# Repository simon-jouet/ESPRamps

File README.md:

# ESPRamps

ESP32 3d printer board for RAMPS

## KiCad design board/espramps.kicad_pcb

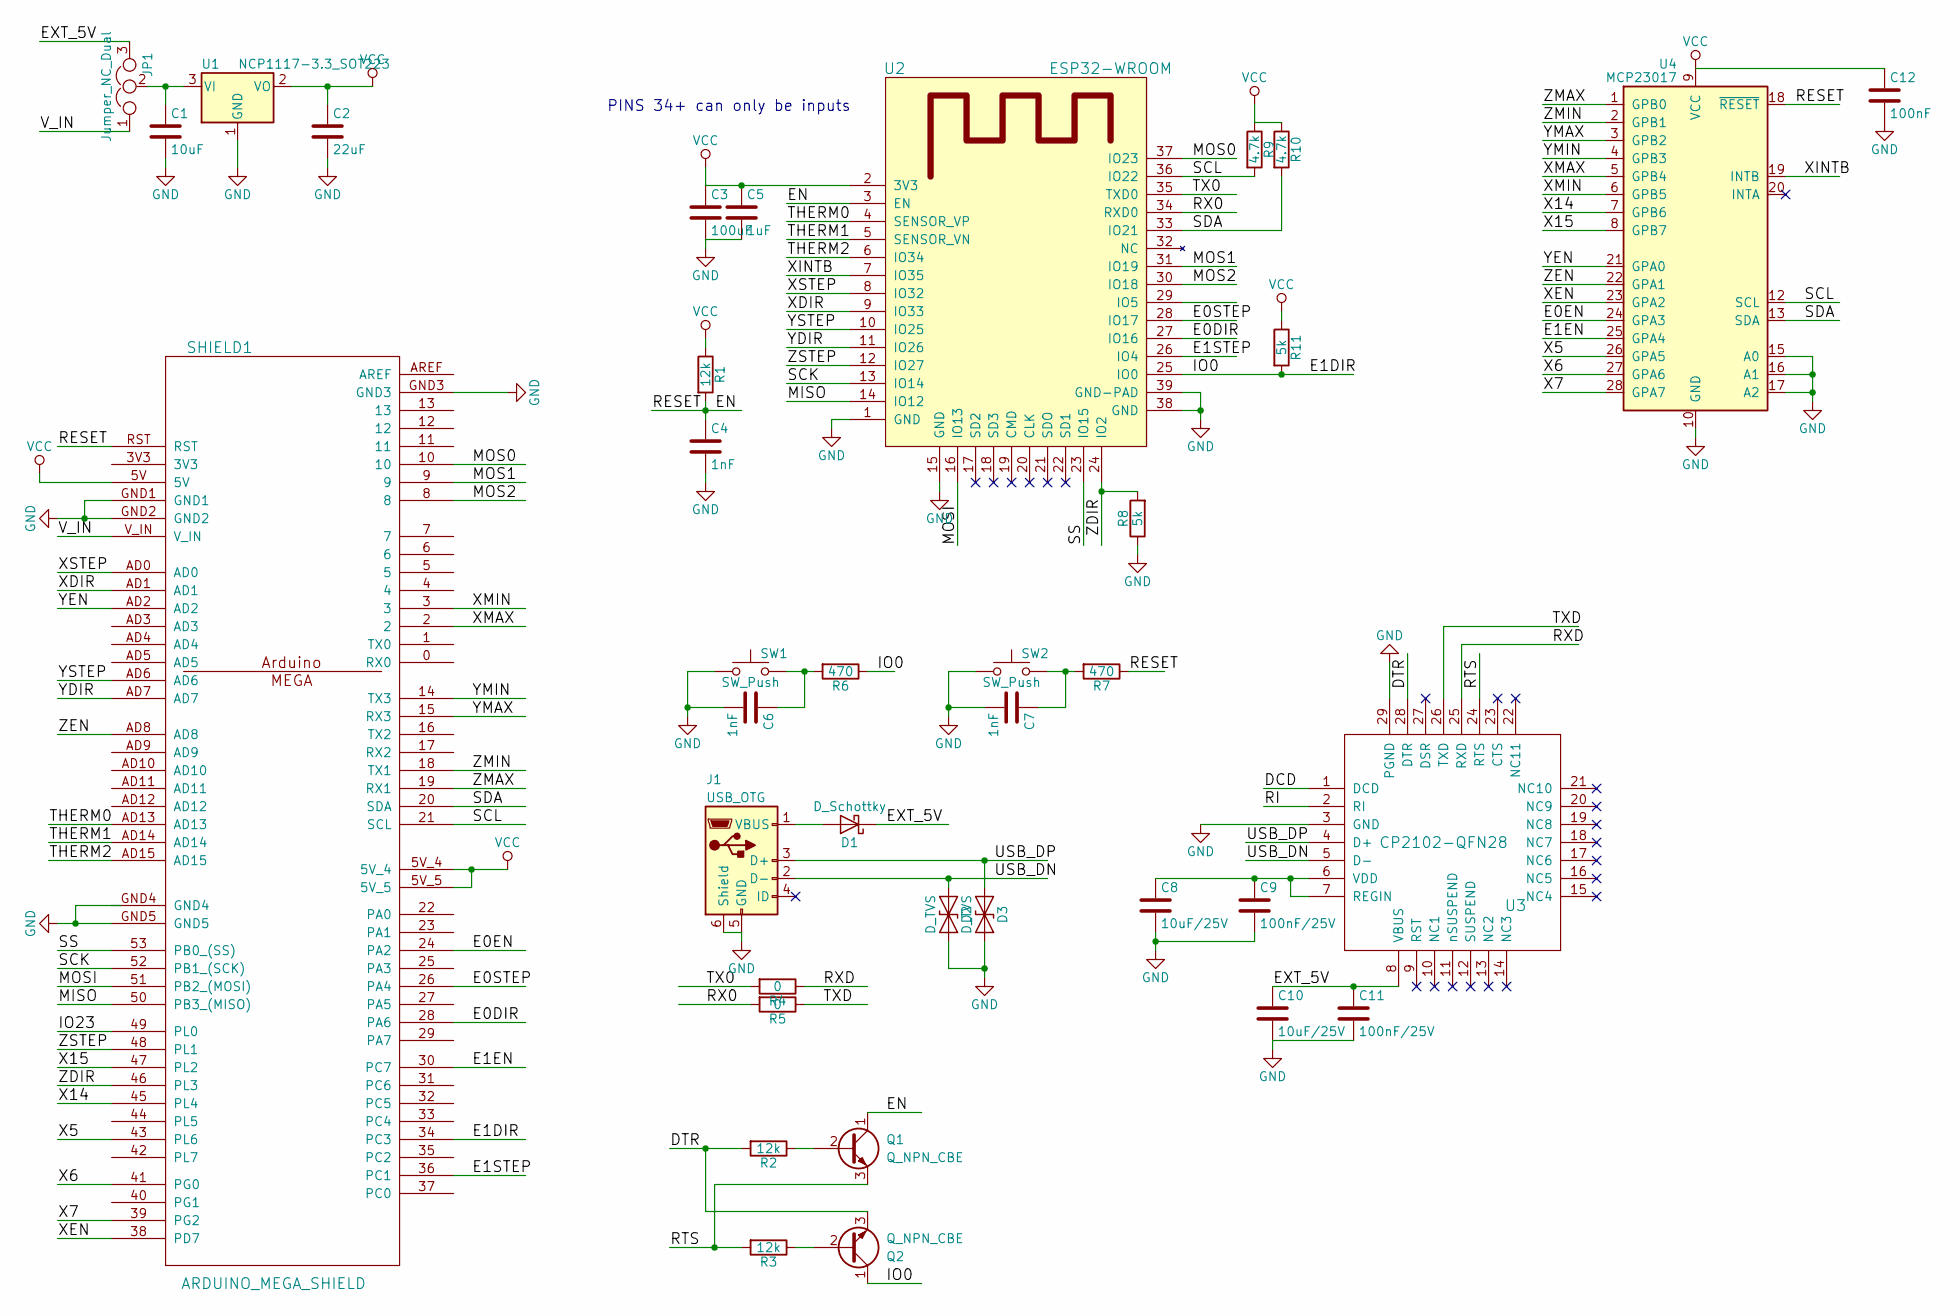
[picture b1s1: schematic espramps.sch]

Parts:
C1: 10uF; C_0805
C2: 22uF; C_0805
C3: 100uF; C_0805
C4, C6, C7: 1nF; C_0805
C5: 1uF; C_0805
C8, C10: 10uF/25V; C_0805
C9, C11: 100nF/25V; C_0805
C12: 100nF; C_0805
D1: D_Schottky; D_SOD-123
D2, D3: D_TVS; D_0603
J1: USB_OTG; USB_Micro-B
JP1: Jumper_NC_Dual; Pin_Header_Straight_1x03_Pitch2.54mm
Q1, Q2: Q_NPN_CBE; SOT-23
R1, R2, R3: 12k; R_0805
R4, R5: 0; R_0805
R6, R7: 470; R_0805
R8, R11: 5k; R_0805
R9, R10: 4.7k; R_0805
SHIELD1: ARDUINO_MEGA_SHIELD; ARDUINO MEGA SHIELD
SW1, SW2: SW_Push; SW_SPST_EVPBF
U1: NCP1117-3.3_SOT223; SOT-223-3Lead_TabPin2
U2: ESP32-WROOM
U3: CP2102-QFN28; QFN-28-1EP_5x5mm_Pitch0.5mm
U4: MCP23017; SOIC-28

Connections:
/DCD: U3.1 (DCD)
/DTR: Q2.3 (E), R2.2, U3.28 (DTR)
/E0DIR: SHIELD1.28 (PA6), U2.27 (IO16)
/E0EN: SHIELD1.24 (PA2), U4.24 (GPA3)
/E0STEP: SHIELD1.26 (PA4), U2.28 (IO17)
/E1DIR: Q2.1 (C), R6.1, R11.2, SHIELD1.34 (PC3), U2.25 (IO0)
/E1EN: SHIELD1.30 (PC7), U4.25 (GPA4)
/E1STEP: SHIELD1.36 (PC1), U2.26 (IO4)
/EN: C4.1, Q1.1 (C), R1.2, R7.1, SHIELD1.RST, U2.3 (EN), U4.18 (~RESET)
/EXT_5V: C10.1, C11.1, D1.1 (K), JP1.3, U3.8 (VBUS)
/IO23: SHIELD1.49 (PL0)
/MISO: SHIELD1.50 (PB3_(MISO)), U2.14 (IO12)
/MOS0: SHIELD1.10, U2.37 (IO23)
/MOS1: SHIELD1.9, U2.31 (IO19)
/MOS2: SHIELD1.8, U2.30 (IO18)
/MOSI: SHIELD1.51 (PB2_(MOSI)), U2.16 (IO13)
/RI: U3.2 (RI)
/RTS: Q1.3 (E), R3.2, U3.24 (RTS)
/RX0: R5.2, U2.34 (RXD0)
/RXD: R4.1, U3.25 (RXD)
/SCK: SHIELD1.52 (PB1_(SCK)), U2.13 (IO14)
/SCL: R9.2, SHIELD1.21 (SCL), U2.36 (IO22), U4.12 (SCL)
/SDA: R10.2, SHIELD1.20 (SDA), U2.33 (IO21), U4.13 (SDA)
/SS: SHIELD1.53 (PB0_(SS)), U2.23 (IO15)
/THERM0: SHIELD1.AD13, U2.4 (SENSOR_VP)
/THERM1: SHIELD1.AD14, U2.5 (SENSOR_VN)
/THERM2: SHIELD1.AD15, U2.6 (IO34)
/TX0: R4.2, U2.35 (TXD0)
/TXD: R5.1, U3.26 (TXD)
/USB_DN: D2.1 (A1), J1.2 (D-), U3.5 (D-)
/USB_DP: D3.1 (A1), J1.3 (D+), U3.4 (D+)
/V_IN: JP1.1, SHIELD1.V_IN
/X5: SHIELD1.43 (PL6), U4.26 (GPA5)
/X6: SHIELD1.41 (PG0), U4.27 (GPA6)
/X7: SHIELD1.39 (PG2), U4.28 (GPA7)
/X14: SHIELD1.45 (PL4), U4.7 (GPB6)
/X15: SHIELD1.47 (PL2), U4.8 (GPB7)
/XDIR: SHIELD1.AD1, U2.9 (IO33)
/XEN: SHIELD1.38 (PD7), U4.23 (GPA2)
/XINTB: U2.7 (IO35), U4.19 (INTB)
/XMAX: SHIELD1.2, U4.5 (GPB4)
/XMIN: SHIELD1.3, U4.6 (GPB5)
/XSTEP: SHIELD1.AD0, U2.8 (IO32)
/YDIR: SHIELD1.AD7, U2.11 (IO26)
/YEN: SHIELD1.AD2, U4.21 (GPA0)
/YMAX: SHIELD1.15 (RX3), U4.3 (GPB2)
/YMIN: SHIELD1.14 (TX3), U4.4 (GPB3)
/YSTEP: SHIELD1.AD6, U2.10 (IO25)
/ZDIR: R8.2, SHIELD1.46 (PL3), U2.24 (IO2)
/ZEN: SHIELD1.AD8, U4.22 (GPA1)
/ZMAX: SHIELD1.19 (RX1), U4.1 (GPB0)
/ZMIN: SHIELD1.18 (TX1), U4.2 (GPB1)
/ZSTEP: SHIELD1.48 (PL1), U2.12 (IO27)
GND: C1.2, C2.2, C3.2, C4.2, C5.2, C6.2, C7.2, C8.2, C9.2, C10.2, C11.2, C12.2, D2.2 (A2), D3.2 (A2), J1.5 (GND), J1.6 (Shield), R8.1, SHIELD1.GND1, SHIELD1.GND2, SHIELD1.GND3, SHIELD1.GND5, SW1.1, SW2.1, U1.1 (GND), U2.1 (GND), U2.15 (GND), U2.38 (GND), U2.39 (GND-PAD), U3.3 (GND), U3.29 (PGND), U4.10 (GND), U4.15 (A0), U4.16 (A1), U4.17 (A2); also elsewhere on the board
unnamed: C1.1, JP1.2, U1.3 (VI)
unnamed 55: C6.1, R6.2, SW1.2; also elsewhere on the board
unnamed 56: C7.1, R7.2, SW2.2; also elsewhere on the board
unnamed: C8.1, C9.1, U3.6 (VDD), U3.7 (REGIN)
unnamed: D1.2 (A), J1.1 (VBUS)
unnamed: Q1.2 (B), R2.1
unnamed: Q2.2 (B), R3.1
VCC: C2.1, C3.1, C5.1, C12.1, R1.1, R9.1, R10.1, R11.1, SHIELD1.5V, SHIELD1.5V_4, SHIELD1.5V_5, U1.2 (VO), U2.2 (3V3), U4.9 (VCC)

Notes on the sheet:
PINS 34+ can only be inputs

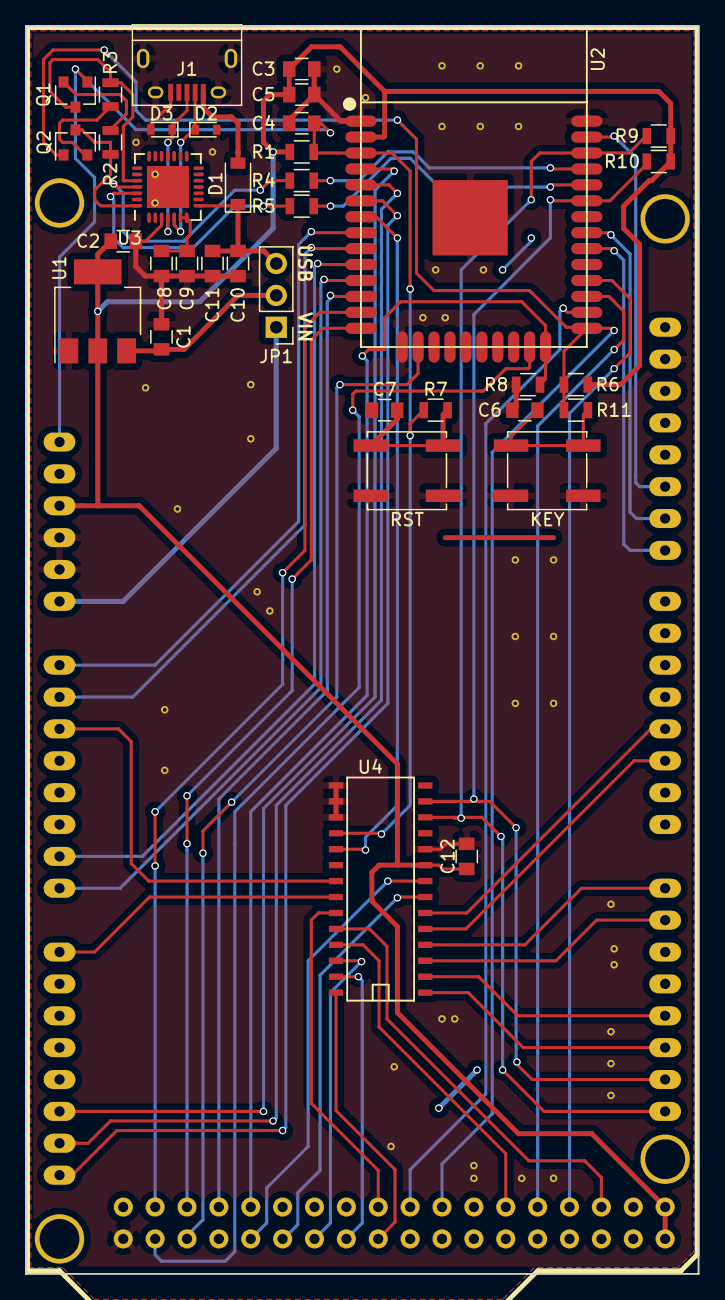
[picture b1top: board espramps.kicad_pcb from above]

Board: 2 copper layers, 53.6 x 99.4 mm, 37 parts (0 on the bottom side), 59 nets.

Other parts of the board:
KEY: SW_Push; SW_SPST_EVPBF
RST: SW_Push; SW_SPST_EVPBF

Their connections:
GND: KEY.1, RST.1; also elsewhere on the board
unnamed 55: KEY.2; also elsewhere on the board
unnamed 56: RST.2; also elsewhere on the board

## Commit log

2017-10-26 First prototype board
2017-12-26 fix zstep/zdir, SOIC package and missing aliases
